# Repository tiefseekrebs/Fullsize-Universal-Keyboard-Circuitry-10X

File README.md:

# FUKC10X — Fullsize Universal Keyboard Circuitry 10X

> 🚧 **Work in Progress** — This PCB has **not yet been prototyped** and currently has **no firmware**.
---

## Introduction

**Fullsize Universal Keyboard Circuitry 10X or fukc10X for short**, is an open-source, full-size (100%) mechanical keyboard PCB designed in KiCad. It's essentially a h87 footprint pcb just with a numpad attached.

This came to life after i wanted to design a Fullsize Keyboard but found out there were no modern opensource full-size keyboard pcbs.

---

## Features
- Dual Indicators. You can have indicator leds for Caps Lock, Scroll Lock and Num Lock directly at the switches for the use with windowed Keycaps and above the numpad in a small cluster.
- Decent layout support with ANSI+ISO Enter, split l-Shift, split r-Shift, split Backspace, split numpad Enter, split numpad plus and split numpad minus (just check the diagramm)
- Supported bottomrows are Tsangan **7U** aswell as **6U** bottom row, like the Realforce R1 87U. (*I will not be adding 6.25u bottom row*)
- Breakeaway onboard USB-C connector, pads for soldering a USB-cable to, as well as a JST connector for the use with a UDB

---

##  Design Files

The files were designed in KiCAD 10.0.
This project uses component symbols and footprints from [AlexandriaLibrary](https://github.com/AcheronProject/AlexandriaLibrary) by AcheronProject, licensed under the BSD-3-Clause License.
Furthermore some symbols and footprints from the [marbastlib](https://github.com/ebastler/marbastlib) are used.

---

## Supported Layouts

---

## Daughterboard Connector

Uses standard 4-pin JST commonly found on all sorts of Keyboard PCBs. Compatible with any daughterboard that follows the [ai03 unified daughterboard standard](https://unified-daughterboard.github.io/#/) pinout.

---

## Firmware

> ⚠️ **Firmware is not yet written.**

| Firmware | Status |
|---|---|
| **[QMK](https://qmk.fm/)** | Planned after i get Prototypes. |
| **[VIAL](https://get.vial.today/)** | Planned after i get Prototypes. |
| **[VIA](https://www.caniusevia.com/)** | Maybe? |

---

## License

This project is licensed under **Creative Commons Attribution-ShareAlike 4.0 International** ([CC BY-SA 4.0](https://creativecommons.org/licenses/by-sa/4.0/deed.en)).
You may share and adapt it, including commercially, with proper attribution.
Modified versions must be distributed under the same license.

---

*This README was written with the help of deepseek-v4-pro because i suck at stuff like this.*

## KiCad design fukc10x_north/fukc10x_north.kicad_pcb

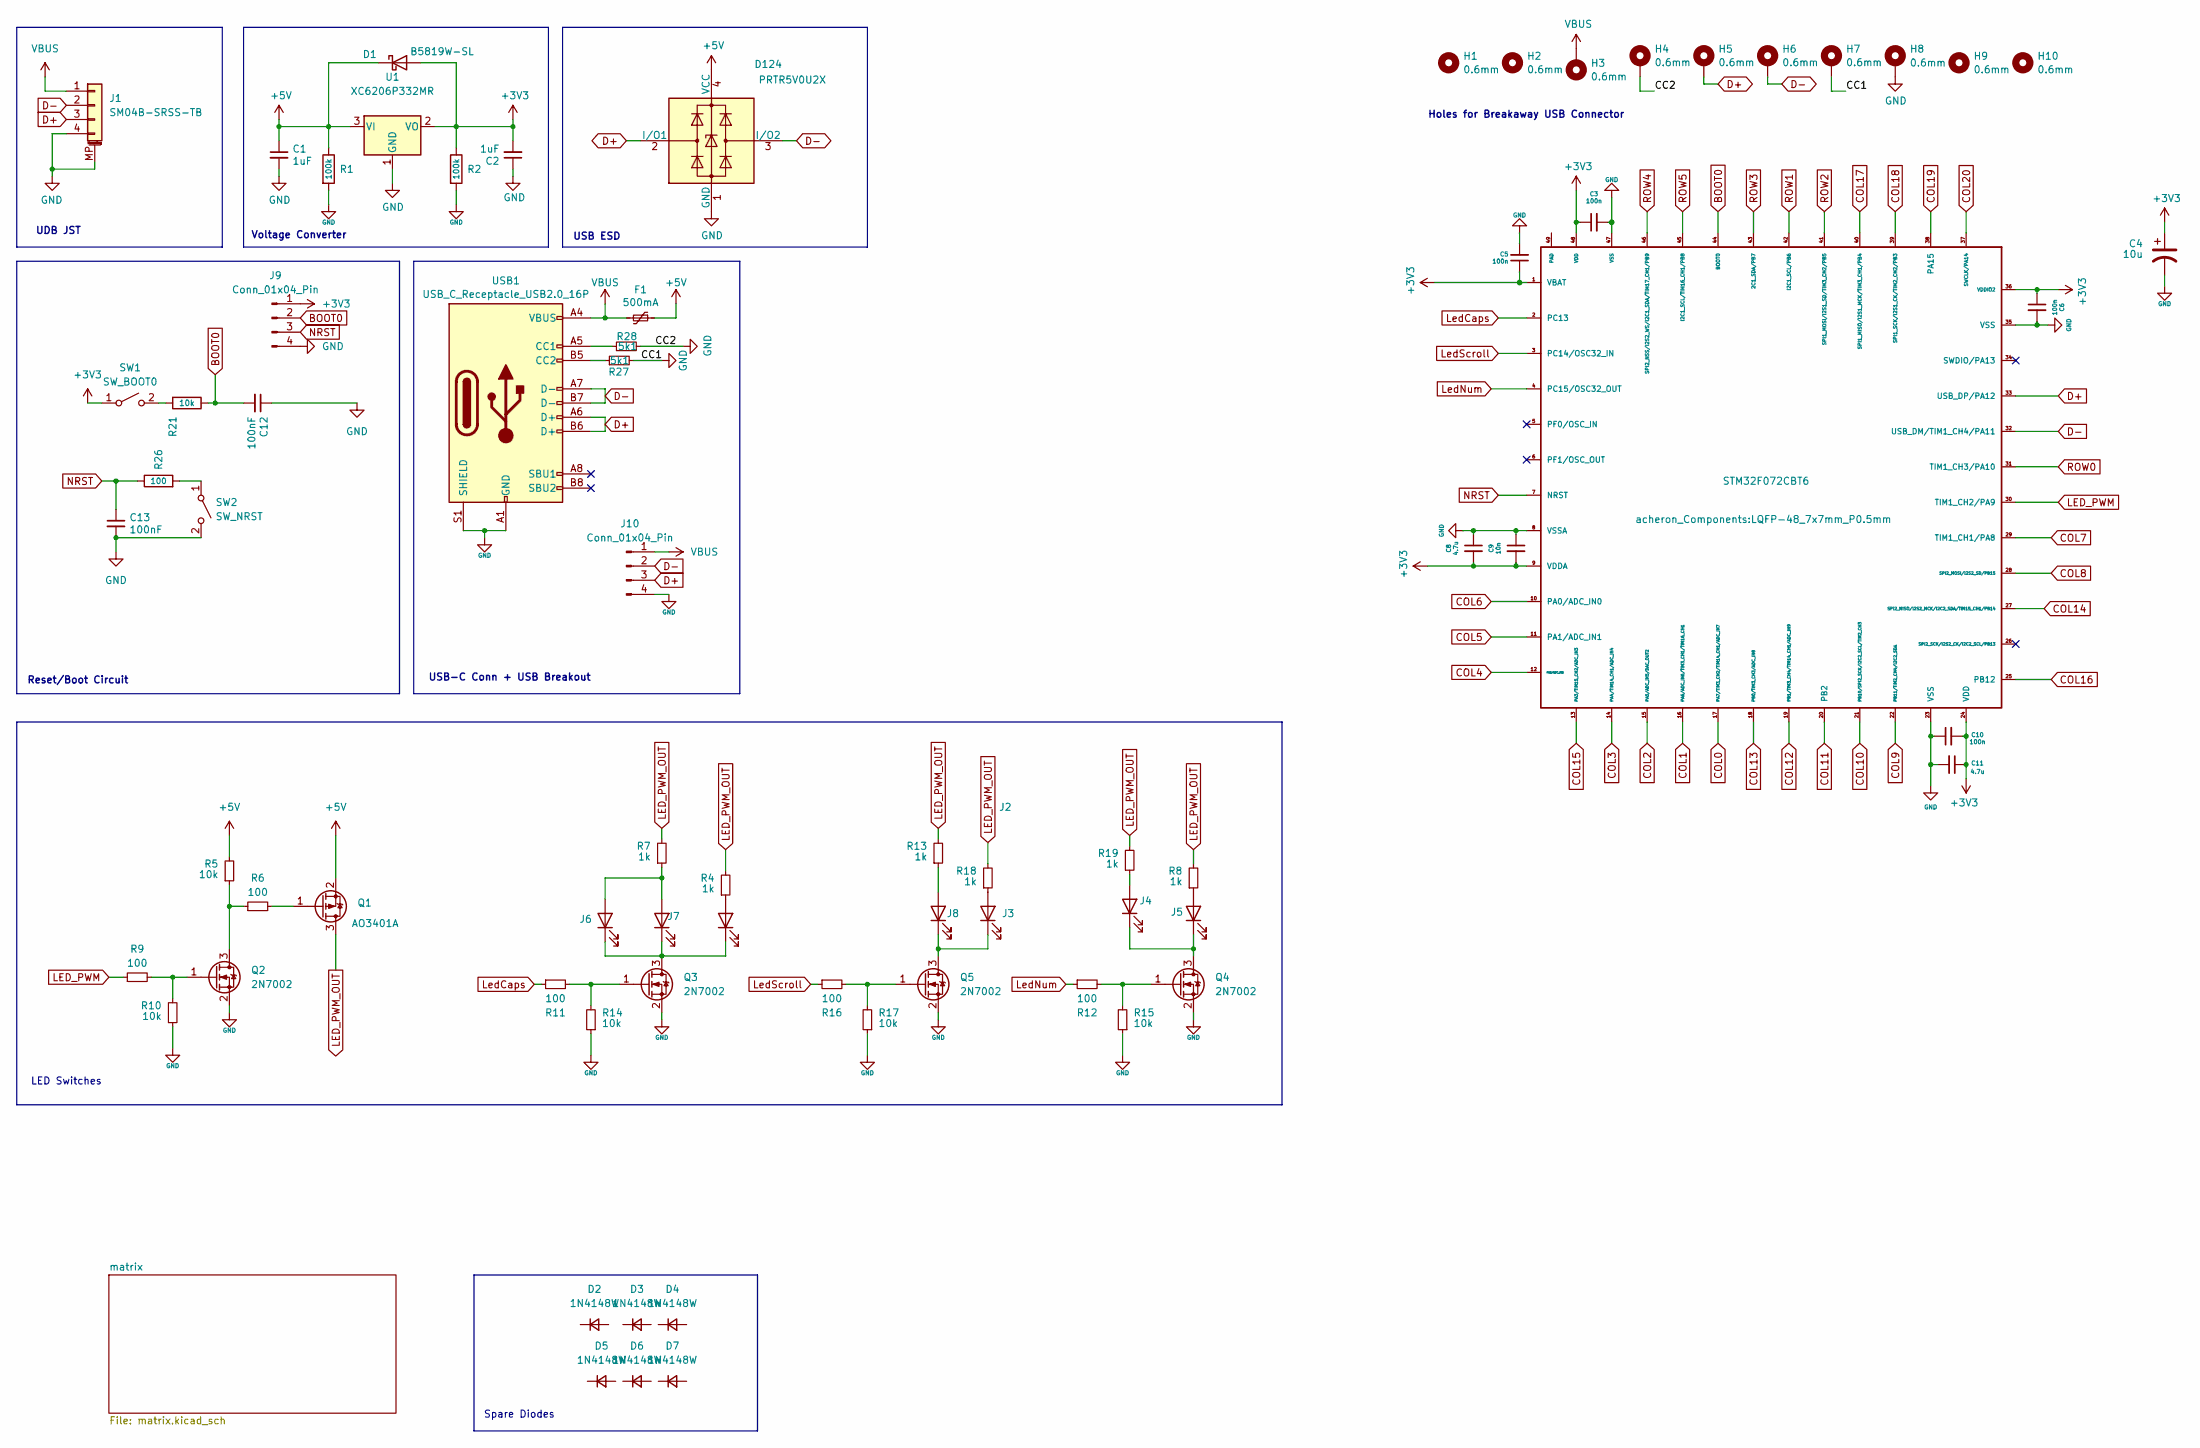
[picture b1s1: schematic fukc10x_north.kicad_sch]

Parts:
C1, C2: 1uF; C_0402_1005Metric; MPN CL05A105KA5NQNC; LCSC C52923
C3, C5: 100n; C_0402_1005Metric
C4: 10u; CP_EIA-3216-10_Kemet-I_Pad1.58x1.35mm_HandSolder; Manufacturer Part Number TAJA106K016RNJ
C6, C10: 100n; C_0402_1005Metric; Manufacturer Part Number CL05B104KB54PNC
C8, C11: 4.7u; C_0402_1005Metric; Manufacturer Part Number CL05A475MP5NRNC
C9: 10n; C_0402_1005Metric; Manufacturer Part Number CL05B103KB5NNNC
C12, C13: 100nF; C_0402_1005Metric; MPN CL05A105KA5NQNC; LCSC C52923
D1: B5819W-SL; D_SOD-123; Manufacturer Part Number B5819W-SL
D2, D3, D4, D5, D6, D7: 1N4148W; D_SOD-123; LCSC C81598
D124: PRTR5V0U2X; SOT-143; MPN PRTR5V0U2X; LCSC C2827688
F1: 500mA; Fuse_1206_3216Metric_Pad1.42x1.75mm_HandSolder; MPN nSMD050; LCSC C69688
H1, H2, H9, H10: 0.6mm; Hole_0.6mm
H3, H4, H5, H6, H7, H8: 0.6mm; Hole_0.6mm_Pad
J1: SM04B-SRSS-TB; JST_SH_SM04B-SRSS-TB_1x04-1MP_P1.00mm_Horizontal; MPN SM04B-SRSS-TB(LF)(SN); LCSC C160404
J2, J3, J4, J5, J8: LED_Conn01x02_Pin; LED_MX_3mm
J6: LED_Conn01x02_Pin; LED_MX_3mm-ROT
J7: LED; LED_MX_3mm
J9, J10: Conn_01x04_Pin; PinHeader_1x4_P2.54mm_Vertical
Q1: AO3401A; SOT-23; Manufacturer Part Number Alpha & Omega Semicon
Q2, Q3, Q4, Q5: 2N7002; SOT-23; Manufacturer Part Number 2N7002
R1, R2: 100k; R_0805_2012Metric; Manufacturer Part Number 0805W8F1003T5E
R4, R7, R8, R13, R18, R19: 1k; R_0402_1005Metric; Manufacturer Part Number 0402WGF1001TCE
R5, R10, R14, R15, R17: 10k; R_0402_1005Metric; Manufacturer Part Number 0402WGF1002TCE
R6, R9, R11, R12, R16: 100; R_0402_1005Metric; Manufacturer Part Number 0402WGF1000TCE
R21: 10k; R_0402_1005Metric; Manufacturer Part Number 0805W8F1003T5E
R26: 100; R_0402_1005Metric; Manufacturer Part Number 0805W8F1003T5E
R27, R28: 5k1; R_0402_1005Metric; MPN 0402WGF5101TCE; LCSC C25905
SW1: SW_BOOT0; SW_SPST_TL3342
SW2: SW_NRST; SW_SPST_TL3342
U1: XC6206P332MR; SOT-23; MPN XC6206P332MR-G; LCSC C5446
U2: STM32F072CBT6; LQFP-48_7x7mm_P0.5mm; MPN STM32F072CBT6; LCSC C81720
USB1: USB_C_Receptacle_USB2.0_16P; USB_C_Receptacle_HRO_TYPE-C-31-M-12; MPN TYPE-C-31-M-12; LCSC C165948

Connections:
+3V3: C2.2, C3.1, C4.1, C5.1, C6.1, C8.2, C9.2, C10.2, C11.1, D1.2 (A), J9.1, R2.1, SW1.1 (A), U1.2 (VO), U2.1 (VBAT), U2.9 (VDDA), U2.24 (VDD), U2.36 (VDDIO2), U2.48 (VDD); also elsewhere on the board
+5V: C1.1, D1.1 (K), D124.4 (VCC), F1.1, Q1.2 (S), R1.1, R5.2, U1.3 (VI)
BOOT0: C12.2, J9.2, R21.1, U2.44 (BOOT0)
COL0: U2.17 (PA7/TIM3_CH2/TIM14_CH1/ADC_IN7); also elsewhere on the board
COL1: U2.16 (PA6/ADC_IN6/TIM3_CH1/TIM16_CH1); also elsewhere on the board
COL2: U2.15 (PA5/ADC_IN5/DAC_OUT2); also elsewhere on the board
COL3: U2.14 (PA4/TIM14_CH1/ADC_IN4); also elsewhere on the board
COL4: U2.12 (PA2/ADC_IN2); also elsewhere on the board
COL5: U2.11 (PA1/ADC_IN1); also elsewhere on the board
COL6: U2.10 (PA0/ADC_IN0); also elsewhere on the board
COL7: U2.29 (TIM1_CH1/PA8); also elsewhere on the board
COL8: U2.28 (SPI2_MOSI/I2S2_SD/PB15); also elsewhere on the board
COL9: U2.22 (PB11/TIM2_CH4/I2C2_SDA); also elsewhere on the board
COL10: U2.21 (PB10/SPI2_SCK/I2C2_SCL/TIM2_CH3); also elsewhere on the board
COL11: U2.20 (PB2); also elsewhere on the board
COL12: U2.19 (PB1/TIM3_CH4/TIM14_CH1/ADC_IN9); also elsewhere on the board
COL13: U2.18 (PB0/TIM3_CH3/ADC_IN8); also elsewhere on the board
COL14: U2.27 (SPI2_MISO/I2S2_MCK/I2C2_SDA/TIM15_CH1/P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); also elsewhere on the board
COL15: U2.13 (PA3/TIM15_CH2/ADC_IN3); also elsewhere on the board
COL16: U2.25 (PB12); also elsewhere on the board
COL17: U2.40 (SPI1_MISO/I2S1_MCK/TIM3_CH1/PB4); also elsewhere on the board
COL18: U2.39 (SPI1_SCK/I2S1_CK/TIM2_CH2/PB3); also elsewhere on the board
COL19: U2.38 (PA15); also elsewhere on the board
COL20: U2.37 (SWCLK/PA14); also elsewhere on the board
D+: D124.2 (I/O1), H5.1 (1_1), J1.3, J10.3, U2.33 (USB_DP/PA12), USB1.A6 (D+), USB1.B6 (D+)
D-: D124.3 (I/O2), H6.1 (1_1), J1.2, J10.2, U2.32 (USB_DM/TIM1_CH4/PA11), USB1.A7 (D-), USB1.B7 (D-)
LED_PWM: R9.1, U2.30 (TIM1_CH2/PA9)
LED_PWM_OUT: Q1.3 (D), R4.2, R7.2, R8.2, R13.2, R18.2, R19.2
LedCaps: R11.1, U2.2 (PC13)
LedNum: R12.1, U2.4 (PC15/OSC32_OUT)
LedScroll: R16.1, U2.3 (PC14/OSC32_IN)
NRST: C13.1, J9.3, R26.1, U2.7 (NRST)
unnamed: J2.2 (A), R4.1
unnamed: J2.1 (K), J6.1 (K), J7.1 (K), Q3.3 (D)
unnamed: J3.2 (A), R18.1
unnamed: J3.1 (K), J8.1 (K), Q5.3 (D)
unnamed: J4.2 (A), R19.1
unnamed: J4.1 (K), J5.1 (K), Q4.3 (D)
unnamed: J5.2 (A), R8.1
unnamed: J6.2 (A), J7.2 (A), R7.1
unnamed: J8.2 (A), R13.1
unnamed: Q1.1 (G), R6.2
unnamed: Q2.3 (D), R5.1, R6.1
unnamed: Q2.1 (G), R9.2, R10.2
unnamed: Q3.1 (G), R11.2, R14.2
unnamed: Q4.1 (G), R12.2, R15.2
unnamed: Q5.1 (G), R16.2, R17.2
unnamed 162: R21.2, SW1.2 (B); also elsewhere on the board
unnamed 163: R26.2, SW2.1 (A); also elsewhere on the board
ROW0: U2.31 (TIM1_CH3/PA10); also elsewhere on the board
ROW1: U2.42 (I2C1_SCL/PB6); also elsewhere on the board
ROW2: U2.41 (SPI1_MOSI/I2S1_SD/TIM3_CH2/PB5); also elsewhere on the board
ROW3: U2.43 (2C1_SDA/PB7); also elsewhere on the board
ROW4: U2.46 (SPI2_NSS/I2S2_WS/I2C1_SDA/TIM17_CH1/PB9); also elsewhere on the board
ROW5: U2.45 (I2C1_SCL/TIM16_CH1/PB8); also elsewhere on the board
VBUS: F1.2, H3.1 (1_1), J1.1, J10.1, USB1.A4 (VBUS), USB1.A9 (VBUS), USB1.B4 (VBUS), USB1.B9 (VBUS)

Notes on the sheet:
Spare Diodes
LED Switches
UDB JST
Voltage Converter
USB ESD
USB-C Conn + USB Breakout
Holes for Breakaway USB Connector
Reset/Boot Circuit

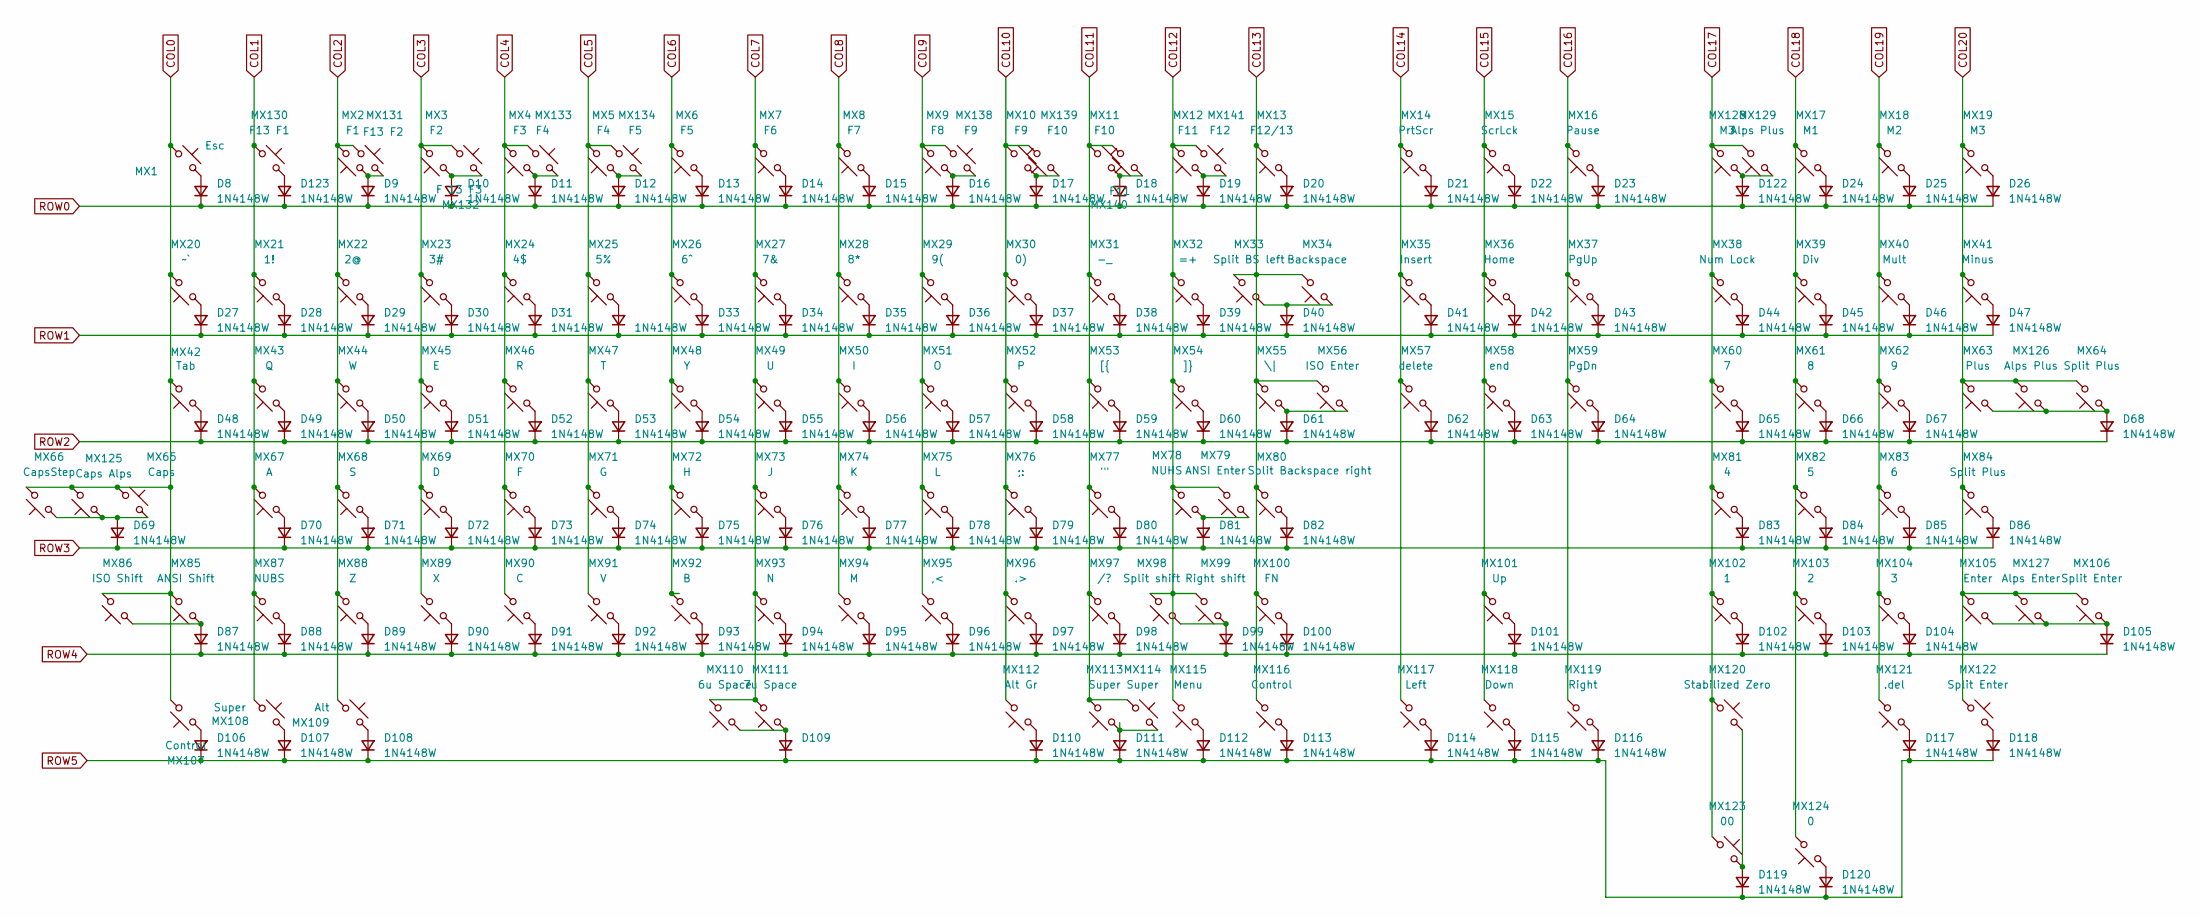
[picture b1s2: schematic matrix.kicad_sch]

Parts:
D8, D9, D10, D11, D12, D13, D14, D15, D16, D17, D18, D19, D20, D21, D22, D23, D24, D25, D26, D27, D28, D29, D30, D31, D32, D33, D34, D35, D36, D37, D38, D39, D40, D41, D42, D43, D44, D45, D46, D47, D48, D49, D50, D51, D52, D53, D54, D55, D56, D57, D58, D59, D60, D61, D62, D63, D64, D65, D66, D67, D68, D69, D70, D71, D72, D73, D74, D75, D76, D77, D78, D79, D80, D81, D82, D83, D84, D85, D86, D87, D88, D89, D90, D91, D92, D93, D94, D95, D96, D97, D98, D99, D100, D101, D102, D103, D104, D105, D106, D107, D108, D109, D110, D111, D112, D113, D114, D115, D116, D117, D118, D119, D120, D122, D123: 1N4148W; D_SOD-123; LCSC C81598
MX1: Esc; MXA100
MX2: F1; MXA100
MX3: F2; MXA100
MX4: F3; MXA100
MX5, MX133: F4; MXA100
MX6, MX134: F5; MXA100
MX7: F6; MXA100
MX8: F7; MXA100
MX9: F8; MXA100
MX10, MX138: F9; MXA100
MX11, MX139: F10; MXA100
MX12, MX140: F11; MXA100
MX13: F12/13; MXA100
MX14: PrtScr; MXA100
MX15: ScrLck; MXA100
MX16: Pause; MXA100
MX17: M1; MXA100
MX18: M2; MXA100
MX19: M3; MXA100
MX20: ~`; MXA100
MX21: 1!; MXA100
MX22: 2@; MXA100
MX23: 3#; MXA100
MX24: 4$; MXA100
MX25: 5%; MXA100
MX26: 6^; MXA100
MX27: 7&; MXA100
MX28: 8*; MXA100
MX29: 9(; MXA100
MX30: 0); MXA100
MX31: -_; MXA100
MX32: =+; MXA100
MX33: Split BS left; MXA100
MX34: Backspace; MXA250
MX35: Insert; MXA100
MX36: Home; MXA100
MX37: PgUp; MXA100
MX38: Num Lock; MXA100
MX39: Div; MXA100
MX40: Mult; MXA100
MX41: Minus; MXA100
MX42: Tab; MXA150
MX43: Q; MXA100
MX44: W; MXA100
MX45: E; MXA100
MX46: R; MXA100
MX47: T; MXA100
MX48: Y; MXA100
MX49: U; MXA100
MX50: I; MXA100
MX51: O; MXA100
MX52: P; MXA100
MX53: [{; MXA100
MX54: ]}; MXA100
MX55: \|; MXA150
MX56: ISO Enter; MXA_ISO_Enter
MX57: delete; MXA100
MX58: end; MXA100
MX59: PgDn; MXA100
MX60: 7; MXA100
MX61: 8; MXA100
MX62: 9; MXA100
MX63: Plus; MX200V
MX64, MX84: Split Plus; MXA100
MX65: Caps; MXA175
MX66: CapsStep; MXA125
MX67: A; MXA100
MX68: S; MXA100
MX69: D; MXA100
MX70: F; MXA100
MX71: G; MXA100
MX72: H; MXA100
MX73: J; MXA100
MX74: K; MXA100
MX75: L; MXA100
MX76: ;:; MXA100
MX77: '"; MXA100
MX78: NUHS; MXA100
MX79: ANSI Enter; MXA225R
MX80: Split Backspace right; MXA100
MX81: 4; MXA100
MX82: 5; MXA100
MX83: 6; MXA100
MX85: ANSI Shift; MXA225
MX86: ISO Shift; MXA125
MX87: NUBS; MXA100
MX88: Z; MXA100
MX89: X; MXA100
MX90: C; MXA100
MX91: V; MXA100
MX92: B; MXA100
MX93: N; MXA100
MX94: M; MXA100
MX95: ,<; MXA100
MX96: .>; MXA100
MX97: /?; MXA100
MX98: Split shift; MXA175
MX99: Right shift; MXA275
MX100: FN; MXA100
MX101: Up; MXA100
MX102: 1; MXA100
MX103: 2; MXA100
MX104: 3; MXA100
MX105: Enter; MX200V
MX106, MX122: Split Enter; MXA100
MX107, MX116: Control; MXA150
MX108, MX114: Super; MXA100
MX109: Alt; MXA150
MX110: 6u Space; MXA600R
MX111: 7u Space; MXA700R
MX112: Alt Gr; MXA150
MX113: Super; MXA150
MX115: Menu; MXA100
MX117: Left; MXA100
MX118: Down; MXA100
MX119: Right; MXA100
MX120: Stabilized Zero; MXA200R
MX121: .del; MXA100
MX123: 00; MXA100
MX124: 0; MXA100
MX125: Caps Alps; SW_Alps_1.75u_STP_1.5
MX126, MX129: Alps Plus; SW_Alps_1u
MX127: Alps Enter; SW_Alps_1u
MX128: M3; MX100
MX130: F13 F1; MXA100
MX131: F13 F2; MXA100
MX132: F 13 F3; MXA100
MX141: F12; MXA100

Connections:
COL0: MX1.2, MX20.2, MX42.2, MX65.1, MX66.2, MX85.2, MX86.2, MX107.2, MX125.2; also elsewhere on the board
COL1: MX21.2, MX43.2, MX67.2, MX87.2, MX108.2, MX130.1; also elsewhere on the board
COL2: MX2.2, MX22.2, MX44.2, MX68.2, MX88.2, MX109.2, MX131.1; also elsewhere on the board
COL3: MX3.2, MX23.2, MX45.2, MX69.2, MX89.2, MX132.1; also elsewhere on the board
COL4: MX4.2, MX24.2, MX46.2, MX70.2, MX90.2, MX133.1; also elsewhere on the board
COL5: MX5.2, MX25.2, MX47.2, MX71.2, MX91.2, MX134.1; also elsewhere on the board
COL6: MX6.2, MX26.2, MX48.2, MX72.2, MX92.2; also elsewhere on the board
COL7: MX7.2, MX27.2, MX49.2, MX73.2, MX93.2, MX110.2, MX111.2; also elsewhere on the board
COL8: MX8.2, MX28.2, MX50.2, MX74.2, MX94.2; also elsewhere on the board
COL9: MX9.2, MX29.2, MX51.2, MX75.2, MX95.2, MX138.1; also elsewhere on the board
COL10: MX10.1, MX30.2, MX52.2, MX76.2, MX96.2, MX112.2, MX139.2; also elsewhere on the board
COL11: MX11.1, MX31.2, MX53.2, MX77.2, MX97.2, MX113.2, MX114.1, MX140.2; also elsewhere on the board
COL12: MX12.2, MX32.2, MX54.2, MX78.2, MX79.2, MX98.2, MX99.2, MX115.2, MX141.1; also elsewhere on the board
COL13: MX13.2, MX33.2, MX34.2, MX55.2, MX56.2, MX80.2, MX100.2, MX116.2; also elsewhere on the board
COL14: MX14.2, MX35.2, MX57.2, MX117.2; also elsewhere on the board
COL15: MX15.2, MX36.2, MX58.2, MX101.2, MX118.2; also elsewhere on the board
COL16: MX16.2, MX37.2, MX59.2, MX119.2; also elsewhere on the board
COL17: MX38.2, MX60.2, MX81.2, MX102.2, MX120.1, MX123.1, MX128.2, MX129.2; also elsewhere on the board
COL18: MX17.2, MX39.2, MX61.2, MX82.2, MX103.2, MX124.2; also elsewhere on the board
COL19: MX18.2, MX40.2, MX62.2, MX83.2, MX104.2, MX121.2; also elsewhere on the board
COL20: MX19.2, MX41.2, MX63.2, MX64.2, MX84.2, MX105.2, MX106.2, MX122.1, MX126.2, MX127.2; also elsewhere on the board
unnamed: D8.2 (A), MX1.1
unnamed: D9.2 (A), MX2.1, MX131.2
unnamed: D10.2 (A), MX3.1, MX132.2
unnamed: D11.2 (A), MX4.1, MX133.2
unnamed: D12.2 (A), MX5.1, MX134.2
unnamed: D13.2 (A), MX6.1
unnamed: D14.2 (A), MX7.1
unnamed: D15.2 (A), MX8.1
unnamed: D16.2 (A), MX9.1, MX138.2
unnamed: D17.2 (A), MX10.2, MX139.1
unnamed: D18.2 (A), MX11.2, MX140.1
unnamed: D19.2 (A), MX12.1, MX141.2
unnamed: D20.2 (A), MX13.1
unnamed: D21.2 (A), MX14.1
unnamed: D22.2 (A), MX15.1
unnamed: D23.2 (A), MX16.1
unnamed: D24.2 (A), MX17.1
unnamed: D25.2 (A), MX18.1
unnamed: D26.2 (A), MX19.1
unnamed: D27.2 (A), MX20.1
unnamed: D28.2 (A), MX21.1
unnamed: D29.2 (A), MX22.1
unnamed: D30.2 (A), MX23.1
unnamed: D31.2 (A), MX24.1
unnamed: D32.2 (A), MX25.1
unnamed: D33.2 (A), MX26.1
unnamed: D34.2 (A), MX27.1
unnamed: D35.2 (A), MX28.1
unnamed: D36.2 (A), MX29.1
unnamed: D37.2 (A), MX30.1
unnamed: D38.2 (A), MX31.1
unnamed: D39.2 (A), MX32.1
unnamed: D40.2 (A), MX33.1, MX34.1
unnamed: D41.2 (A), MX35.1
unnamed: D42.2 (A), MX36.1
unnamed: D43.2 (A), MX37.1
unnamed: D44.2 (A), MX38.1
unnamed: D45.2 (A), MX39.1
unnamed: D46.2 (A), MX40.1
unnamed: D47.2 (A), MX41.1
unnamed: D48.2 (A), MX42.1
unnamed: D49.2 (A), MX43.1
unnamed: D50.2 (A), MX44.1
unnamed: D51.2 (A), MX45.1
unnamed: D52.2 (A), MX46.1
unnamed: D53.2 (A), MX47.1
unnamed: D54.2 (A), MX48.1
unnamed: D55.2 (A), MX49.1
unnamed: D56.2 (A), MX50.1
unnamed: D57.2 (A), MX51.1
unnamed: D58.2 (A), MX52.1
unnamed: D59.2 (A), MX53.1
unnamed: D60.2 (A), MX54.1
unnamed: D61.2 (A), MX55.1, MX56.1
unnamed: D62.2 (A), MX57.1
unnamed: D63.2 (A), MX58.1
unnamed: D64.2 (A), MX59.1
unnamed: D65.2 (A), MX60.1
unnamed: D66.2 (A), MX61.1
unnamed: D67.2 (A), MX62.1
unnamed: D68.2 (A), MX63.1, MX64.1, MX126.1
unnamed: D69.2 (A), MX65.2, MX66.1, MX125.1
unnamed: D70.2 (A), MX67.1
unnamed: D71.2 (A), MX68.1
unnamed: D72.2 (A), MX69.1
unnamed: D73.2 (A), MX70.1
unnamed: D74.2 (A), MX71.1
unnamed: D75.2 (A), MX72.1
unnamed: D76.2 (A), MX73.1
unnamed: D77.2 (A), MX74.1
unnamed: D78.2 (A), MX75.1
unnamed: D79.2 (A), MX76.1
unnamed: D80.2 (A), MX77.1
unnamed: D81.2 (A), MX78.1, MX79.1
unnamed: D82.2 (A), MX80.1
unnamed: D83.2 (A), MX81.1
unnamed: D84.2 (A), MX82.1
unnamed: D85.2 (A), MX83.1
unnamed: D86.2 (A), MX84.1
unnamed: D87.2 (A), MX85.1, MX86.1
unnamed: D88.2 (A), MX87.1
unnamed: D89.2 (A), MX88.1
unnamed: D90.2 (A), MX89.1
unnamed: D91.2 (A), MX90.1
unnamed: D92.2 (A), MX91.1
unnamed: D93.2 (A), MX92.1
unnamed: D94.2 (A), MX93.1
unnamed: D95.2 (A), MX94.1
unnamed: D96.2 (A), MX95.1
unnamed: D97.2 (A), MX96.1
unnamed: D98.2 (A), MX97.1
unnamed: D99.2 (A), MX98.1, MX99.1
unnamed: D100.2 (A), MX100.1
unnamed: D101.2 (A), MX101.1
unnamed: D102.2 (A), MX102.1
unnamed: D103.2 (A), MX103.1
unnamed: D104.2 (A), MX104.1
unnamed: D105.2 (A), MX105.1, MX106.1, MX127.1
unnamed: D106.2 (A), MX107.1
unnamed: D107.2 (A), MX108.1
unnamed: D108.2 (A), MX109.1
unnamed: D109.2 (A), MX110.1, MX111.1
unnamed: D110.2 (A), MX112.1
unnamed: D111.2 (A), MX113.1, MX114.2
unnamed: D112.2 (A), MX115.1
unnamed: D113.2 (A), MX116.1
unnamed: D114.2 (A), MX117.1
unnamed: D115.2 (A), MX118.1
unnamed: D116.2 (A), MX119.1
unnamed: D117.2 (A), MX121.1
unnamed: D118.2 (A), MX122.2
unnamed: D119.2 (A), MX120.2, MX123.2
unnamed: D120.2 (A), MX124.1
unnamed: D122.2 (A), MX128.1, MX129.1
unnamed: D123.2 (A), MX130.2
ROW0: D8.1 (K), D9.1 (K), D10.1 (K), D11.1 (K), D12.1 (K), D13.1 (K), D14.1 (K), D15.1 (K), D16.1 (K), D17.1 (K), D18.1 (K), D19.1 (K), D20.1 (K), D21.1 (K), D22.1 (K), D23.1 (K), D24.1 (K), D25.1 (K), D26.1 (K), D122.1 (K), D123.1 (K); also elsewhere on the board
ROW1: D27.1 (K), D28.1 (K), D29.1 (K), D30.1 (K), D31.1 (K), D32.1 (K), D33.1 (K), D34.1 (K), D35.1 (K), D36.1 (K), D37.1 (K), D38.1 (K), D39.1 (K), D40.1 (K), D41.1 (K), D42.1 (K), D43.1 (K), D44.1 (K), D45.1 (K), D46.1 (K), D47.1 (K); also elsewhere on the board
ROW2: D48.1 (K), D49.1 (K), D50.1 (K), D51.1 (K), D52.1 (K), D53.1 (K), D54.1 (K), D55.1 (K), D56.1 (K), D57.1 (K), D58.1 (K), D59.1 (K), D60.1 (K), D61.1 (K), D62.1 (K), D63.1 (K), D64.1 (K), D65.1 (K), D66.1 (K), D67.1 (K), D68.1 (K); also elsewhere on the board
ROW3: D69.1 (K), D70.1 (K), D71.1 (K), D72.1 (K), D73.1 (K), D74.1 (K), D75.1 (K), D76.1 (K), D77.1 (K), D78.1 (K), D79.1 (K), D80.1 (K), D81.1 (K), D82.1 (K), D83.1 (K), D84.1 (K), D85.1 (K), D86.1 (K); also elsewhere on the board
ROW4: D87.1 (K), D88.1 (K), D89.1 (K), D90.1 (K), D91.1 (K), D92.1 (K), D93.1 (K), D94.1 (K), D95.1 (K), D96.1 (K), D97.1 (K), D98.1 (K), D99.1 (K), D100.1 (K), D101.1 (K), D102.1 (K), D103.1 (K), D104.1 (K), D105.1 (K); also elsewhere on the board
ROW5: D106.1 (K), D107.1 (K), D108.1 (K), D109.1 (K), D110.1 (K), D111.1 (K), D112.1 (K), D113.1 (K), D114.1 (K), D115.1 (K), D116.1 (K), D117.1 (K), D118.1 (K), D119.1 (K), D120.1 (K); also elsewhere on the board

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
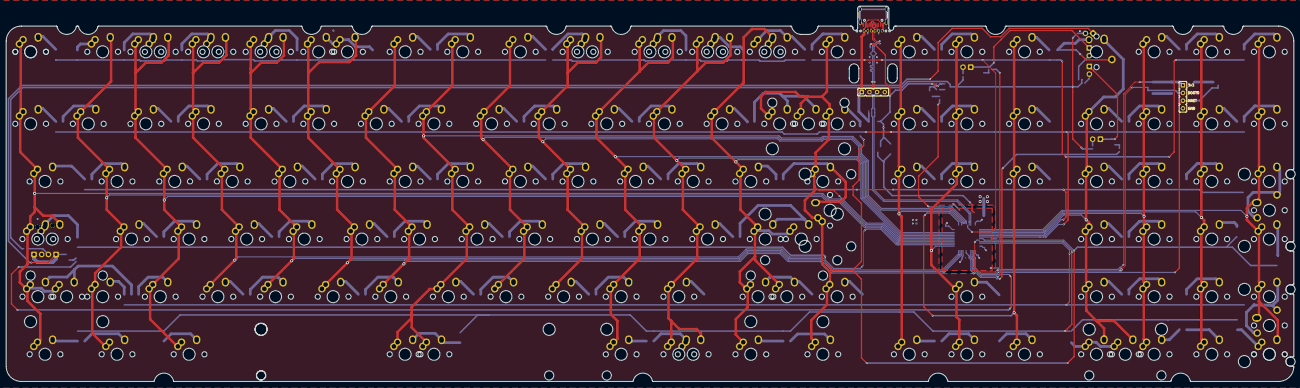
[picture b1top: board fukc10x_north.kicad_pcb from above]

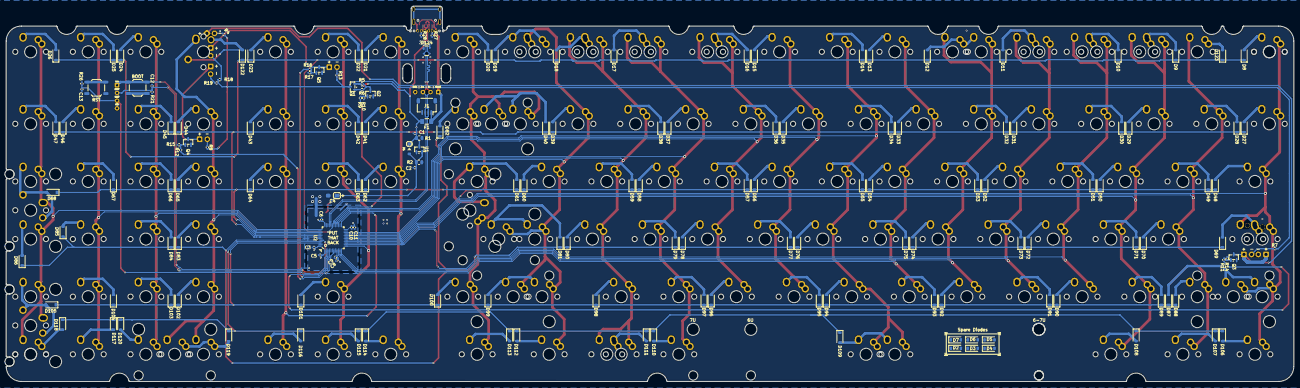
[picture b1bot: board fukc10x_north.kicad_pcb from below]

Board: 2 copper layers, 425.7 x 124.1 mm, 326 parts (168 on the bottom side), 174 nets.

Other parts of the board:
BOOT: SW_BOOT0; SW_SPST_TL3342
RST: SW_NRST; SW_SPST_TL3342

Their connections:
+3V3: BOOT.1 (A); also elsewhere on the board
unnamed 162: BOOT.2 (B); also elsewhere on the board
unnamed 163: RST.1 (A); also elsewhere on the board

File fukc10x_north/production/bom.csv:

Designator,Footprint,Quantity,Value,LCSC Part #
BOOT,SW_SPST_TL3342,1,SW_BOOT0,
"C1, C2",0402,2,1uF,C52923
"C10, C3, C5, C6",0402,4,100n,
"C11, C8",0402,2,4.7u,
"C12, C13",0402,2,100nF,C52923
C4,CP_EIA-3216-10_Kemet-I_Pad1.58x1.35mm_HandSolder,1,10u,
C9,0402,1,10n,
D1,D_SOD-123,1,B5819W-SL,
"D10, D100, D101, D102, D103, D104, D105, D106, D107, D108, D109, D11, D110, D111, D112, D113, D114, D115, D116, D117, D118, D119, D12, D120, D122, D123, D13, D14, D15, D16, D17, D18, D19, D2, D20, D21, D22, D23, D24, D25, D26, D27, D28, D29, D3, D30, D31, D32, D33, D34, D35, D36, D37, D38, D39, D4, D40, D41, D42, D43, D44, D45, D46, D47, D48, D49, D5, D50, D51, D52, D53, D54, D55, D56, D57, D58, D59, D6, D60, D61, D62, D63, D64, D65, D66, D67, D68, D69, D7, D70, D71, D72, D73, D74, D75, D76, D77, D78, D79, D8, D80, D81, D82, D83, D84, D85, D86, D87, D88, D89, D9, D90, D91, D92, D93, D94, D95, D96, D97, D98, D99",D_SOD-123,121,1N4148W,C81598 
D124,SOT-143,1,PRTR5V0U2X,C2827688
F1,1206,1,500mA,C69688
J1,JST_SH_SM04B-SRSS-TB_1x04-1MP_P1.00mm_Horizontal,1,SM04B-SRSS-TB,C160404
"J10, J9",PinHeader_1x4_P2.54mm_Vertical,2,Conn_01x04_Pin,
Q1,SOT-23,1,AO3401A,
"Q2, Q3, Q4, Q5",SOT-23,4,2N7002,
"R1, R2",0805,2,100k,
"R10, R14, R15, R17, R21, R5",0402,6,10k,
"R11, R12, R16, R26, R6, R9",0402,6,100,
"R13, R18, R19, R4, R7, R8",0402,6,1k,
"R27, R28",0402,2,5k1,C25905
RST,SW_SPST_TL3342,1,SW_NRST,
U1,SOT-23,1,XC6206P332MR,C5446
U2,LQFP-48_7x7mm_P0.5mm,1,STM32F072CBT6,C81720
USB1,USB_C_Receptacle_HRO_TYPE-C-31-M-12,1,USB_C_Receptacle_USB2.0_16P,C165948

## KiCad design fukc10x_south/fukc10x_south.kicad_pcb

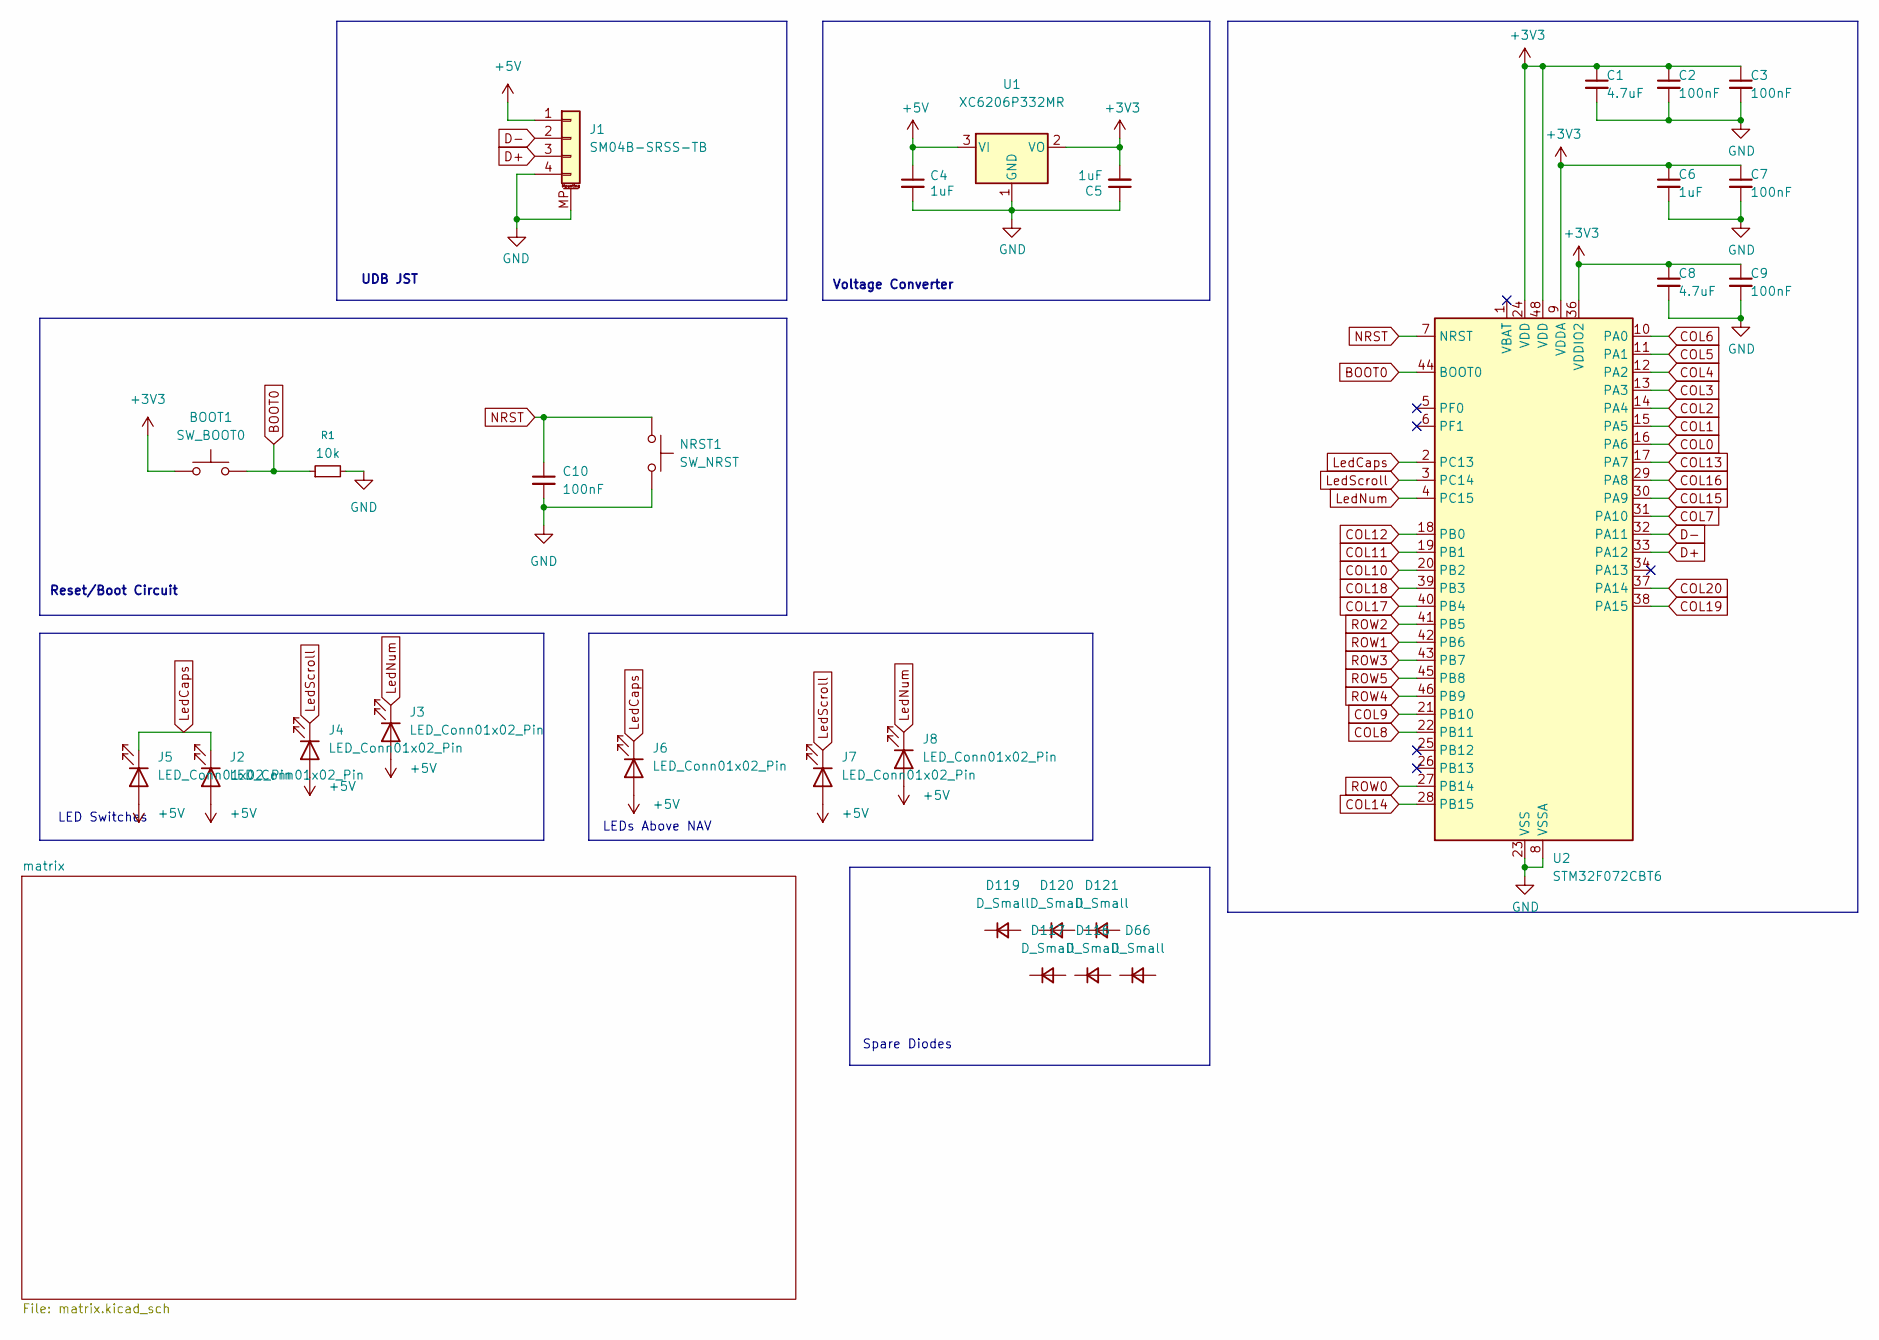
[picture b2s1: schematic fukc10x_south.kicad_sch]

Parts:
BOOT1: SW_BOOT0; SW_SPST_TL3342; LCSC C318884
C1, C8: 4.7uF; C_0402_1005Metric; MPN CL05A475MP5NRNC; LCSC C23733
C2, C3, C7, C9: 100nF; C_0402_1005Metric; MPN CL05B104KO5NNNC; LCSC C1525
C4, C5, C6: 1uF; C_0402_1005Metric; MPN CL05A105KA5NQNC; LCSC C52923
C10: 100nF; C_0402_1005Metric; LCSC C1525
D66, D116, D117, D119, D120, D121: D_Small; D_SOD-123; LCSC C81598
J1: SM04B-SRSS-TB; JST_SH_SM04B-SRSS-TB_1x04-1MP_P1.00mm_Horizontal; MPN SM04B-SRSS-TB(LF)(SN); LCSC C160404
J2, J3, J4, J6, J7, J8: LED_Conn01x02_Pin; LED_MX_3mm
J5: LED_Conn01x02_Pin; LED_MX_3mm-ROT
NRST1: SW_NRST; SW_SPST_TL3342; LCSC C318884
R1: 10k; R_0402_1005Metric; LCSC C25744
U1: XC6206P332MR; SOT-23; MPN XC6206P332MR-G; LCSC C5446
U2: STM32F072CBT6; LQFP-48_7x7mm_P0.5mm; MPN STM32F072CBT6; LCSC C81720

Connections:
+3V3: BOOT1.1, C1.1, C2.1, C3.1, C5.2, C6.1, C7.1, C8.1, C9.1, U1.2 (VO), U2.9 (VDDA), U2.24 (VDD), U2.36 (VDDIO2), U2.48 (VDD)
+5V: C4.1, J1.1, J2.2 (A), J3.2 (A), J4.2 (A), J5.2 (A), J6.2 (A), J7.2 (A), J8.2 (A), U1.3 (VI)
BOOT0: BOOT1.2, R1.1, U2.44 (BOOT0)
COL0: U2.16 (PA6); also elsewhere on the board
COL1: U2.15 (PA5); also elsewhere on the board
COL2: U2.14 (PA4); also elsewhere on the board
COL3: U2.13 (PA3); also elsewhere on the board
COL4: U2.12 (PA2); also elsewhere on the board
COL5: U2.11 (PA1); also elsewhere on the board
COL6: U2.10 (PA0); also elsewhere on the board
COL7: U2.31 (PA10); also elsewhere on the board
COL8: U2.22 (PB11); also elsewhere on the board
COL9: U2.21 (PB10); also elsewhere on the board
COL10: U2.20 (PB2); also elsewhere on the board
COL11: U2.19 (PB1); also elsewhere on the board
COL12: U2.18 (PB0); also elsewhere on the board
COL13: U2.17 (PA7); also elsewhere on the board
COL14: U2.28 (PB15); also elsewhere on the board
COL15: U2.30 (PA9); also elsewhere on the board
COL16: U2.29 (PA8); also elsewhere on the board
COL17: U2.40 (PB4); also elsewhere on the board
COL18: U2.39 (PB3); also elsewhere on the board
COL19: U2.38 (PA15); also elsewhere on the board
COL20: U2.37 (PA14); also elsewhere on the board
D+: J1.3, U2.33 (PA12)
D-: J1.2, U2.32 (PA11)
GND: C1.2, C2.2, C3.2, C4.2, C5.1, C6.2, C7.2, C8.2, C9.2, C10.2, J1.4, J1.MP (MountPin), NRST1.2, R1.2, U1.1 (GND), U2.8 (VSSA), U2.23 (VSS), U2.35 (VSS), U2.47 (VSS)
LedCaps: J2.1 (K), J5.1 (K), J6.1 (K), U2.2 (PC13)
LedNum: J3.1 (K), J8.1 (K), U2.4 (PC15)
LedScroll: J4.1 (K), J7.1 (K), U2.3 (PC14)
NRST: C10.1, NRST1.1, U2.7 (NRST)
ROW0: U2.27 (PB14); also elsewhere on the board
ROW1: U2.42 (PB6); also elsewhere on the board
ROW2: U2.41 (PB5); also elsewhere on the board
ROW3: U2.43 (PB7); also elsewhere on the board
ROW4: U2.46 (PB9); also elsewhere on the board
ROW5: U2.45 (PB8); also elsewhere on the board

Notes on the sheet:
Spare Diodes
LEDs Above NAV
LED Switches
UDB JST
Voltage Converter
Reset/Boot Circuit
